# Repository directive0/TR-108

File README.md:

#
This repository hosts a set of design documents for the TR-108 Picorder. A Picorder is a Raspberry Pi based handheld device that records and displays sensor data for immediate analysis. The TR-108 is designed to use a Raspberry Pi Zero W, a set of custom designed PCBs, and a 3D printed enclosure to achieve this goal. This project, along with [PicorderOS](https://squaredwave.com/wiki/index.php?title=PicorderOS) attempts to be a single self contained solution for anyone wishing to build their own Picorder.

## What is included:

- The design_docs folder contains a crude SVG file that shows the 2D layout of the original design, mostly to scale. The SVG includes a crude wiring diagram.

- The pcb_design folder contains KiCad files of the proposed printed circuit board to replace the original perfboard prototype. These files can be used to produce and test PCBs.

- The enclosure_design folder contains STLs (incomplete) and a .blend file containing the raw construction file for a complete enclosure, based closely on the DST Tricorder toy.

## What is not yet included:

- There are no assembly instructions. I hope to produce some in the future.

While it is not required, if you make a picorder using this repository I would appreciate you sharing photos or videos your build with me at chris@squaredwave.com.

For a more regularly updated description of this project please visit the [wiki](https://squaredwave.com/wiki/index.php?title=Picorder)

Originally designed by Chris Barrett in 2017. I consider this project to be "Open Hardware", and as such is free to use, modify distribute or sell. It comes with no promise of support or warranty.

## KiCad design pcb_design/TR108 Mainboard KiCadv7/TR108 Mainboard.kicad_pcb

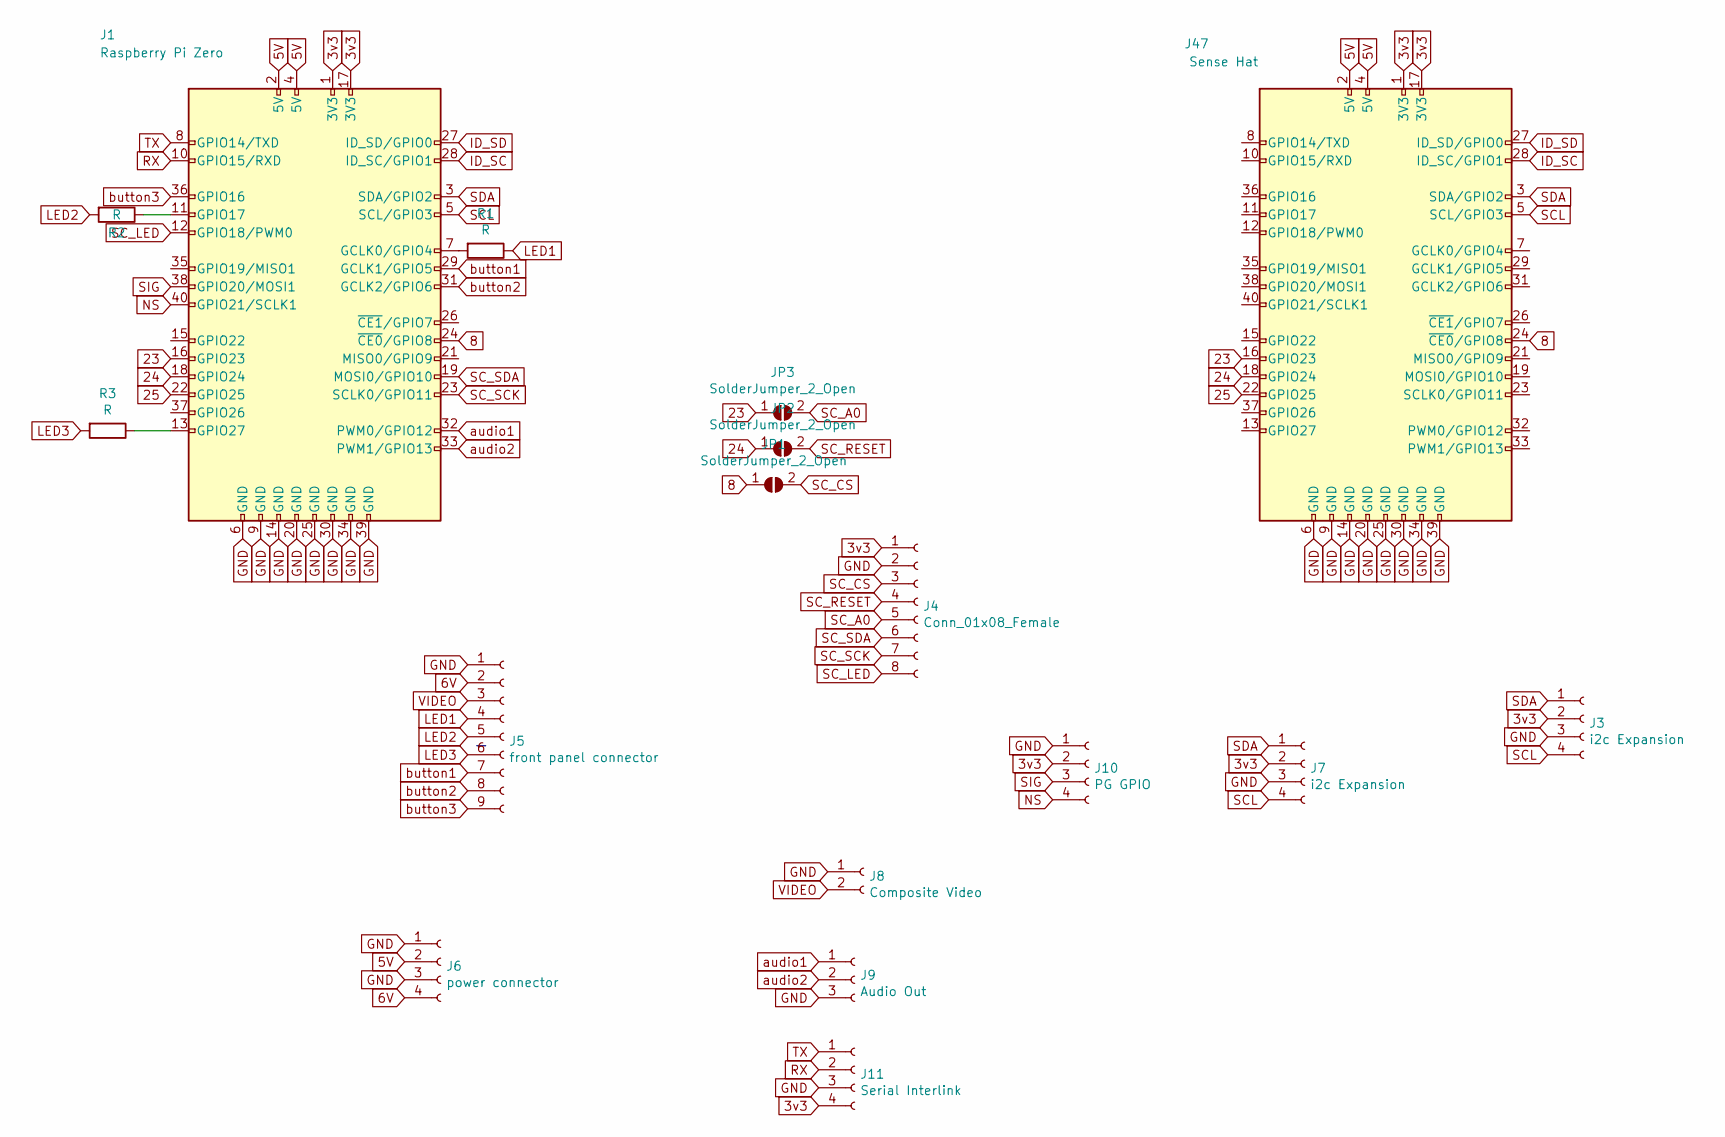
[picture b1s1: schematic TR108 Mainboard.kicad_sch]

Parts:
J1: Raspberry Pi Zero; PinHeader_2x20_P2.54mm_Vertical
J3, J7: i2c Expansion; PinHeader_1x04_P2.54mm_Vertical
J4: Conn_01x08_Female; PinHeader_1x08_P2.54mm_Vertical
J5: front panel connector; PinHeader_1x09_P2.54mm_Vertical
J6: power connector; PinHeader_1x04_P2.54mm_Vertical
J8: Composite Video; PinHeader_1x02_P2.54mm_Vertical
J9: Audio Out; PinHeader_1x03_P2.54mm_Vertical
J10: PG GPIO; PinHeader_1x04_P2.54mm_Vertical
J11: Serial Interlink; PinHeader_1x04_P2.54mm_Vertical
J47: Sense Hat; PinHeader_2x20_P2.54mm_Vertical
JP1, JP2, JP3: SolderJumper_2_Open; SolderJumper-2_P1.3mm_Open_RoundedPad1.0x1.5mm
R1, R2, R3: R; R_0805_2012Metric_Pad1.20x1.40mm_HandSolder

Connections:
3v3: J1.1 (3V3), J1.17 (3V3), J3.2, J4.1, J7.2, J10.2, J11.4, J47.1 (3V3), J47.17 (3V3); also elsewhere on the board
5V: J1.2 (5V), J1.4 (5V), J6.2, J47.2 (5V), J47.4 (5V); also elsewhere on the board
6V: J5.2, J6.4
8: J1.24 (~CE0/GPIO8), J47.24 (~CE0/GPIO8), JP1.1 (A); also elsewhere on the board
23: J1.16 (GPIO23), J47.16 (GPIO23), JP3.1 (A); also elsewhere on the board
24: J1.18 (GPIO24), J47.18 (GPIO24), JP2.1 (A); also elsewhere on the board
25: J1.22 (GPIO25), J47.22 (GPIO25); also elsewhere on the board
GND: J1.6 (GND), J1.9 (GND), J1.14 (GND), J1.20 (GND), J1.25 (GND), J1.30 (GND), J1.34 (GND), J1.39 (GND), J3.3, J4.2, J5.1, J6.1, J6.3, J7.3, J8.1, J9.3, J10.1, J11.3, J47.6 (GND), J47.9 (GND), J47.14 (GND), J47.20 (GND), J47.25 (GND), J47.30 (GND), J47.34 (GND), J47.39 (GND); also elsewhere on the board
ID_SC: J1.28 (ID_SC/GPIO1), J47.28 (ID_SC/GPIO1); also elsewhere on the board
ID_SD: J1.27 (ID_SD/GPIO0), J47.27 (ID_SD/GPIO0); also elsewhere on the board
LED1: J5.4, R1.1
LED2: J5.5, R2.2
LED3: J5.6, R3.2
NS: J1.40 (GPIO21/SCLK1), J10.4
unnamed: J1.7 (GCLK0/GPIO4), R1.2
unnamed: J1.11 (GPIO17), R2.1
unnamed: J1.13 (GPIO27), R3.1
RX: J1.10 (GPIO15/RXD), J11.2
SCL: J1.5 (SCL/GPIO3), J3.4, J7.4, J47.5 (SCL/GPIO3); also elsewhere on the board
SC_A0: J4.5, JP3.2 (B)
SC_CS: J4.3, JP1.2 (B)
SC_LED: J1.12 (GPIO18/PWM0), J4.8
SC_RESET: J4.4, JP2.2 (B)
SC_SCK: J1.23 (SCLK0/GPIO11), J4.7
SC_SDA: J1.19 (MOSI0/GPIO10), J4.6
SDA: J1.3 (SDA/GPIO2), J3.1, J7.1, J47.3 (SDA/GPIO2); also elsewhere on the board
SIG: J1.38 (GPIO20/MOSI1), J10.3
TX: J1.8 (GPIO14/TXD), J11.1
VIDEO: J5.3, J8.2
audio1: J1.32 (PWM0/GPIO12), J9.1
audio2: J1.33 (PWM1/GPIO13), J9.2
button1: J1.29 (GCLK1/GPIO5), J5.7
button2: J1.31 (GCLK2/GPIO6), J5.8
button3: J1.36 (GPIO16), J5.9

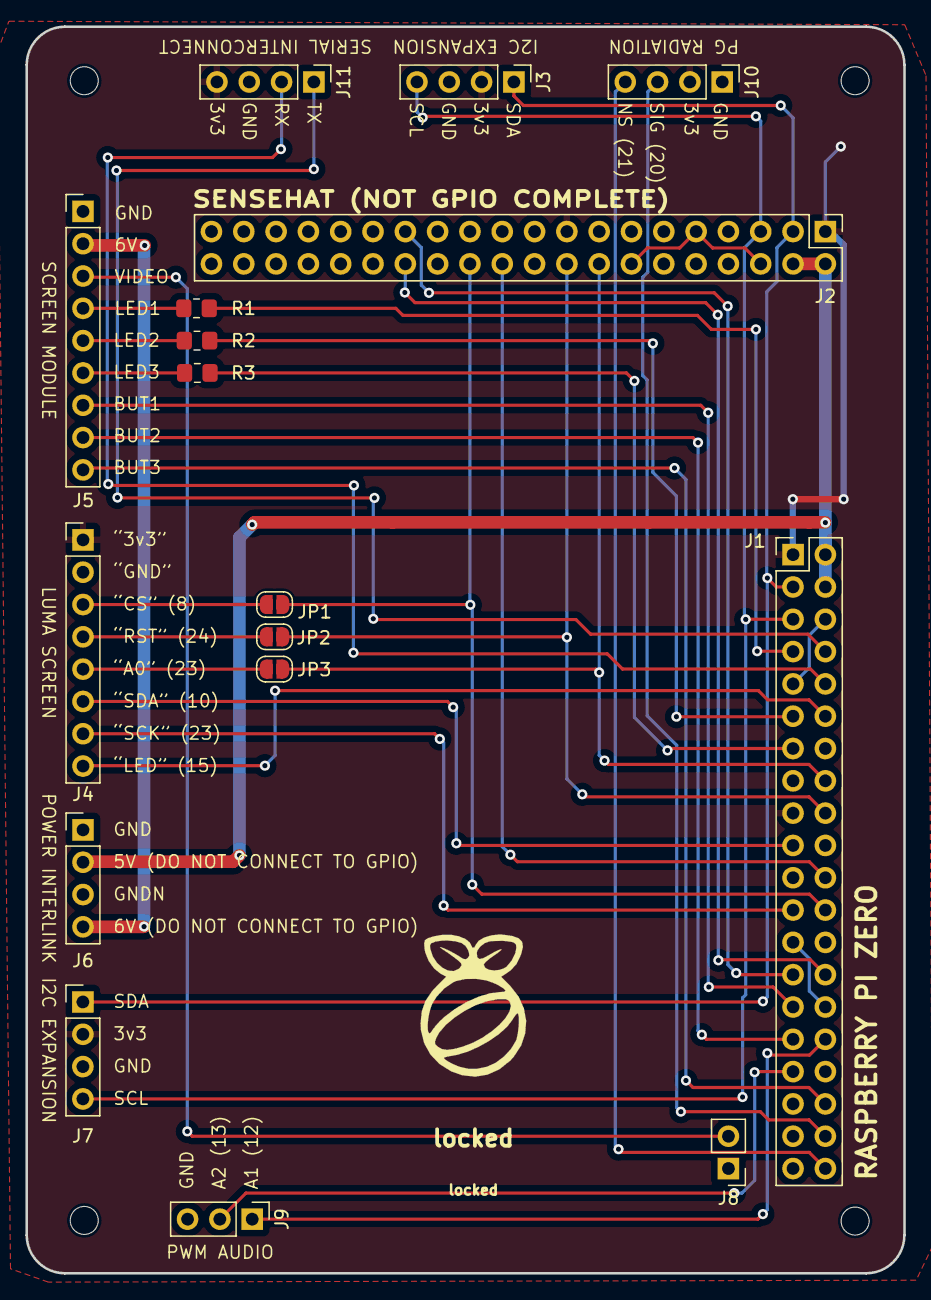
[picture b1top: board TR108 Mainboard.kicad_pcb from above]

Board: 2 copper layers, 69.0 x 98.0 mm, 17 parts (0 on the bottom side), 34 nets.

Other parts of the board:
J2: Sense Hat; PinHeader_2x20_P2.54mm_Vertical

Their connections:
3v3: J2.1 (3V3), J2.17 (3V3); also elsewhere on the board
5V: J2.2 (5V), J2.4 (5V); also elsewhere on the board
8: J2.24 (~CE0/GPIO8); also elsewhere on the board
23: J2.16 (GPIO23); also elsewhere on the board
24: J2.18 (GPIO24); also elsewhere on the board
25: J2.22 (GPIO25); also elsewhere on the board
GND: J2.6 (GND), J2.9 (GND), J2.14 (GND), J2.20 (GND), J2.25 (GND), J2.30 (GND), J2.34 (GND), J2.39 (GND); also elsewhere on the board
ID_SC: J2.28 (ID_SC/GPIO1); also elsewhere on the board
ID_SD: J2.27 (ID_SD/GPIO0); also elsewhere on the board
SCL: J2.5 (SCL/GPIO3); also elsewhere on the board
SDA: J2.3 (SDA/GPIO2); also elsewhere on the board

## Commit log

2021-06-16 File populate
2021-06-16 README update
2021-06-29 Update to PCB
2022-05-18 mass update - new blend and pcb
2022-05-18 trim
2022-05-18 STL changes
2024-04-08 cleanup, Blend update, new PCB
